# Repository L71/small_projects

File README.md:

Some minor projects

* Eurorack blank panels (Ponoko design)
* Eurorack power supply to breadboard adapter
* Eurorack tiny current measurement help PCB
* E-Switch TL2285 breadboard adapter
* Eurorack Mini PSU (switching w Tracopower switch DC converter)
* Breadboard PSU for synth experiments, provides +/- 12V from a USB PSU
* Capacitive touch pad 2x2 test board
* Eurorack +5V adapter with DC-DC converter to get +5V from the -12V rail

These projects are licensed CC BY-SA, Lars Bengtsson 2015-2016.
https://creativecommons.org/licenses/

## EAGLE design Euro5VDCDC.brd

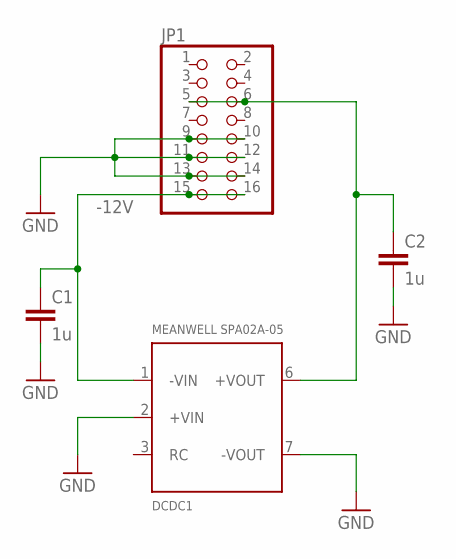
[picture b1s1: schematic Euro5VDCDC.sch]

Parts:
C1, C2: 1u; C1206K
DCDC1: MEANWELL SPA02A-05; MEANWELL_SPA02
JP1: PINHD-2X8; 2X08

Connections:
-12V: C1.1, DCDC1.1 (-VIN), JP1.15, JP1.16
GND: C1.2, C2.2, DCDC1.2 (+VIN), DCDC1.7 (-VOUT), JP1.9, JP1.10, JP1.11, JP1.12, JP1.13, JP1.14
unnamed: C2.1, DCDC1.6 (+VOUT), JP1.5, JP1.6

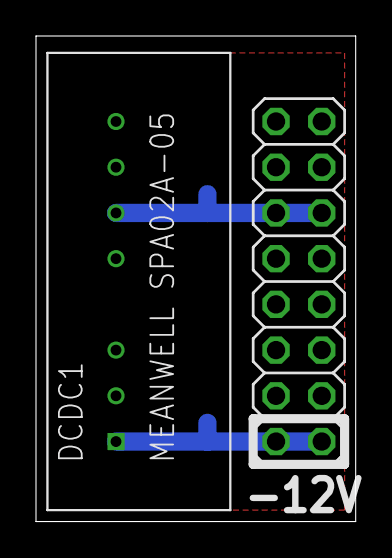
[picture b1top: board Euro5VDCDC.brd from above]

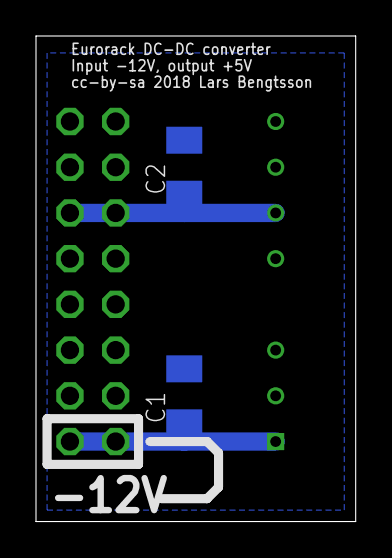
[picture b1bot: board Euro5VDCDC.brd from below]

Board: 2 copper layers, 17.8 x 27.0 mm, 4 parts (2 on the bottom side), 3 nets.

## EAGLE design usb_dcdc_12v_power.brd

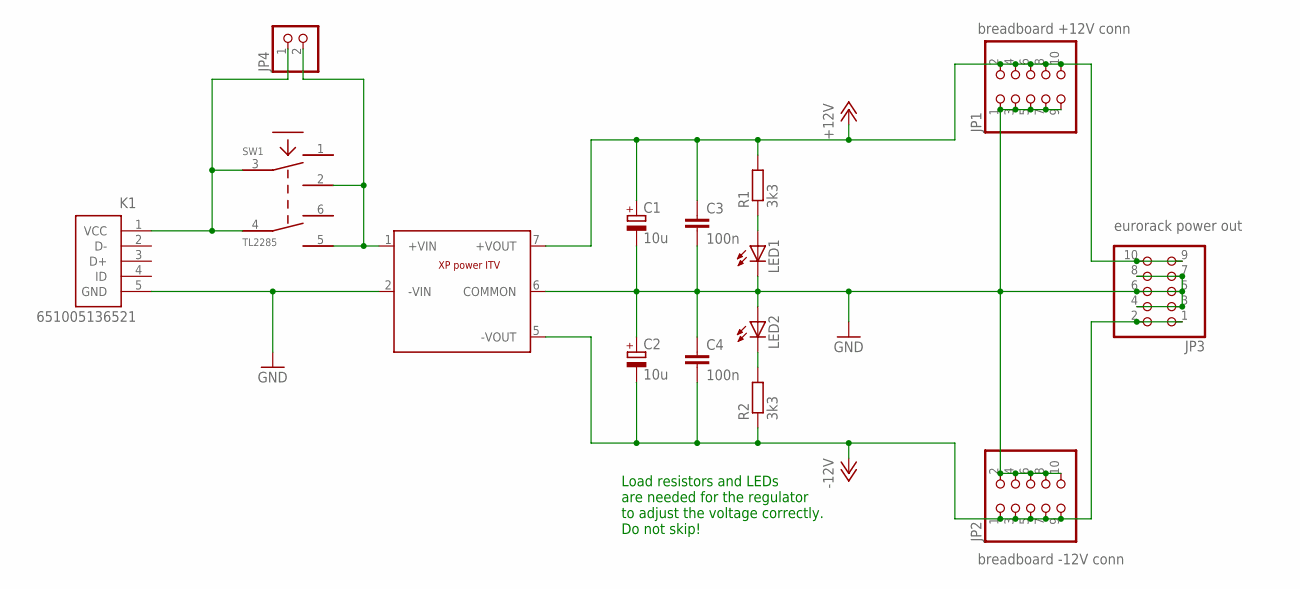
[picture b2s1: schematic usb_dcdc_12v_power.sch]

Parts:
C1, C2: 10u; E2,5-5
C3, C4: 100n; C025-025X050
JP1: breadboard +12V conn; 2X05
JP2: breadboard -12V conn; 2X05
JP3: eurorack power out; 2X05
JP4: PINHD-1X2; 1X02
K1: 651005136521
LED1, LED2: LED3MM
R1, R2: 3k3; 0207/2V
SW1: TL2285; TL2285_PCB
U$1: XP_POWER_ITV; DC_CONV_SIP_STD

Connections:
+12V: C1.+, C3.1, JP1.2, JP1.4, JP1.6, JP1.8, JP1.10, JP3.9, JP3.10, R1.2, U$1.7 (+VOUT)
-12V: C2.-, C4.2, JP2.1, JP2.3, JP2.5, JP2.7, JP2.9, JP3.1, JP3.2, R2.1, U$1.5 (-VOUT)
GND: C1.-, C2.+, C3.2, C4.1, JP1.1, JP1.3, JP1.5, JP1.7, JP1.9, JP2.2, JP2.4, JP2.6, JP2.8, JP2.10, JP3.3, JP3.4, JP3.5, JP3.6, JP3.7, JP3.8, K1.5 (GND), LED1.K (C), LED2.A, U$1.2 (-VIN), U$1.6 (COMMON)
unnamed: JP4.2, SW1.2, SW1.5, U$1.1 (+VIN)
unnamed: JP4.1, K1.1 (VCC), SW1.3, SW1.4
unnamed: LED1.A, R1.1
unnamed: LED2.K (C), R2.2

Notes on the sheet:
Load resistors and LEDs are needed for the regulator to adjust the voltage correctly. Do not skip!

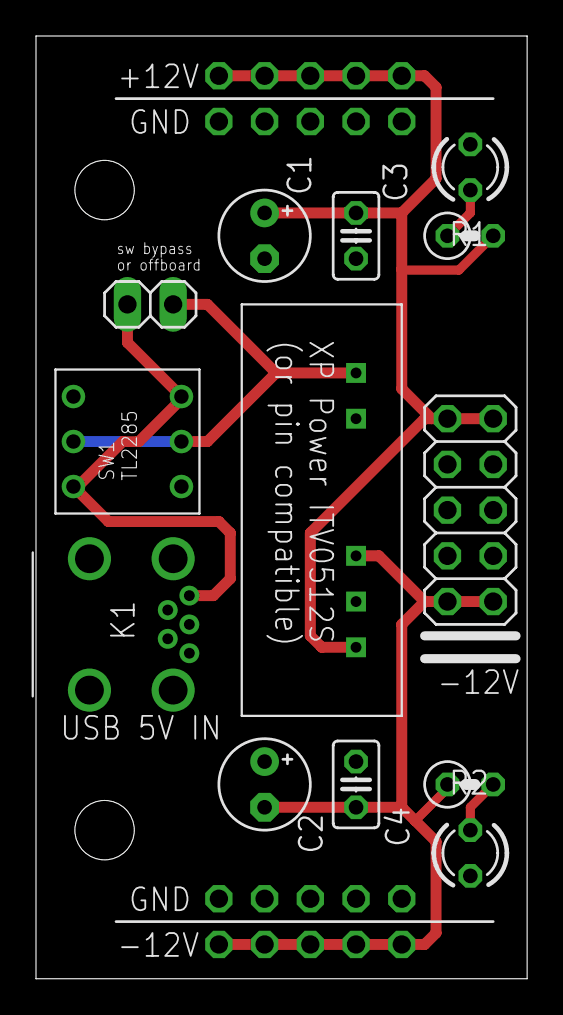
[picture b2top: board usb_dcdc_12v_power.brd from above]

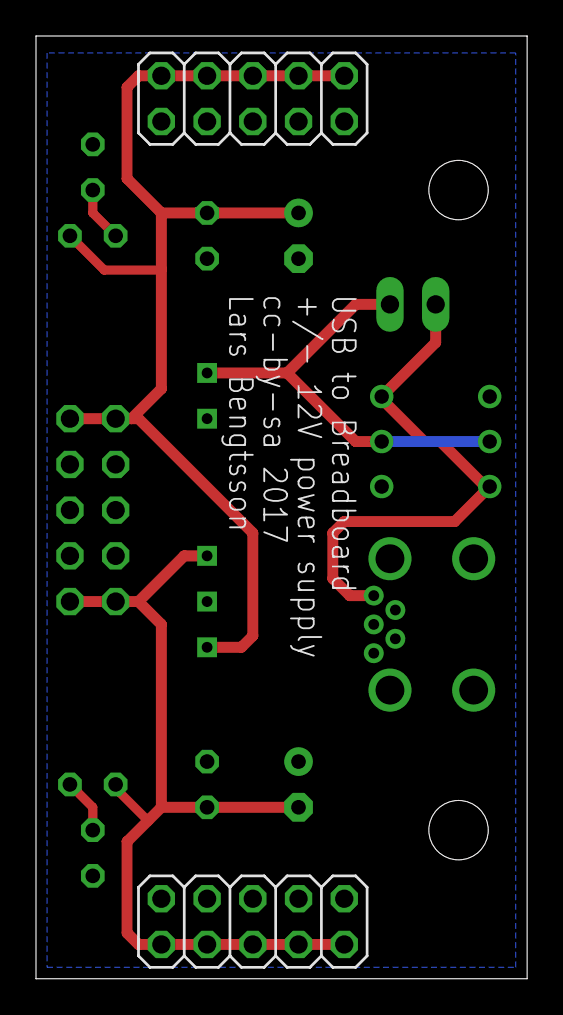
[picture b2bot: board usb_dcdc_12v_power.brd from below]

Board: 2 copper layers, 27.3 x 52.4 mm, 15 parts (2 on the bottom side), 7 nets.

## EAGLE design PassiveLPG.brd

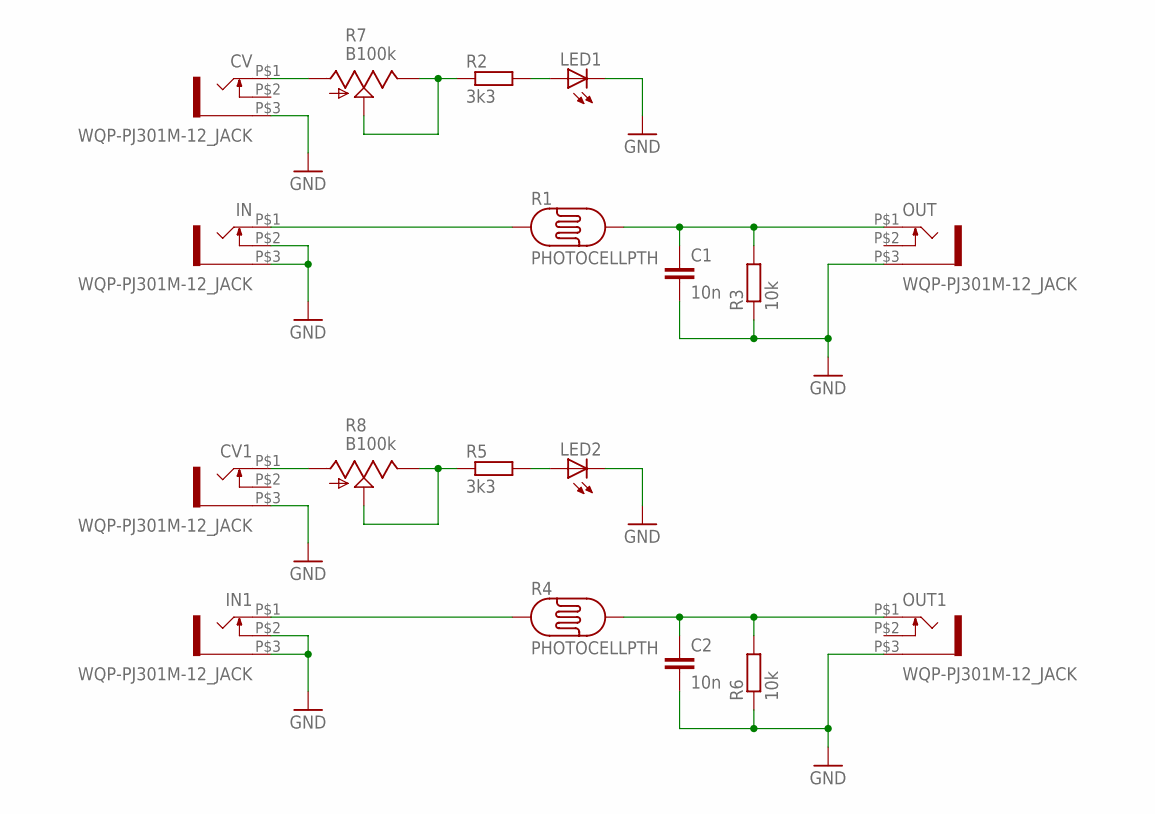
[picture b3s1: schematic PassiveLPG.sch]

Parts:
C1, C2: 10n; C050-025X075
CV, CV1: WQP-PJ301M-12_JACK
IN, IN1: WQP-PJ301M-12_JACK
LED1, LED2: LED5MM
OUT, OUT1: WQP-PJ301M-12_JACK
R1, R4: PHOTOCELLPTH; PHOTOCELL
R2, R5: 3k3; 0207/7
R3, R6: 10k; 0207/7
R7, R8: B100k; ALPS_POT_VERTICAL

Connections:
GND: C1.2, C2.2, CV.P$3 (1), CV1.P$3 (1), IN.P$2 (3), IN.P$3 (1), IN1.P$2 (3), IN1.P$3 (1), LED1.K (C), LED2.K (C), OUT.P$3 (1), OUT1.P$3 (1), R3.1, R6.1
unnamed: CV.P$1 (2), R7.P$3 (A)
unnamed: R2.1, R7.P$1 (E), R7.P$2 (S)
unnamed: IN.P$1 (2), R1.1
unnamed: C1.1, OUT.P$1 (2), R1.2, R3.2
unnamed: LED1.A, R2.2
unnamed: IN1.P$1 (2), R4.1
unnamed: C2.1, OUT1.P$1 (2), R4.2, R6.2
unnamed: R5.1, R8.P$1 (E), R8.P$2 (S)
unnamed: CV1.P$1 (2), R8.P$3 (A)
unnamed: LED2.A, R5.2

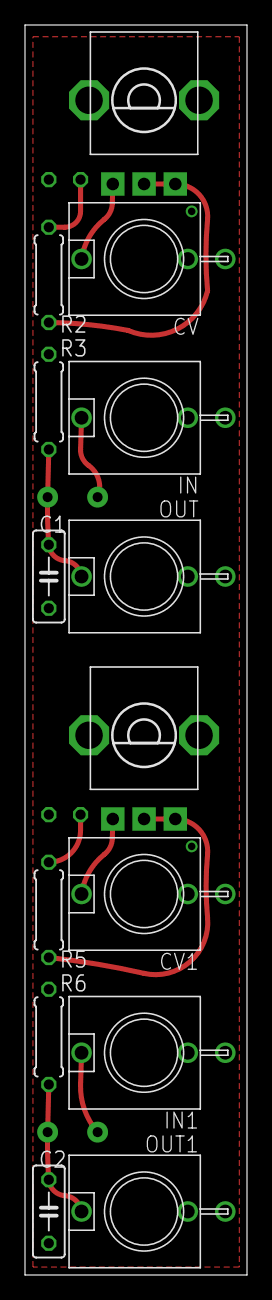
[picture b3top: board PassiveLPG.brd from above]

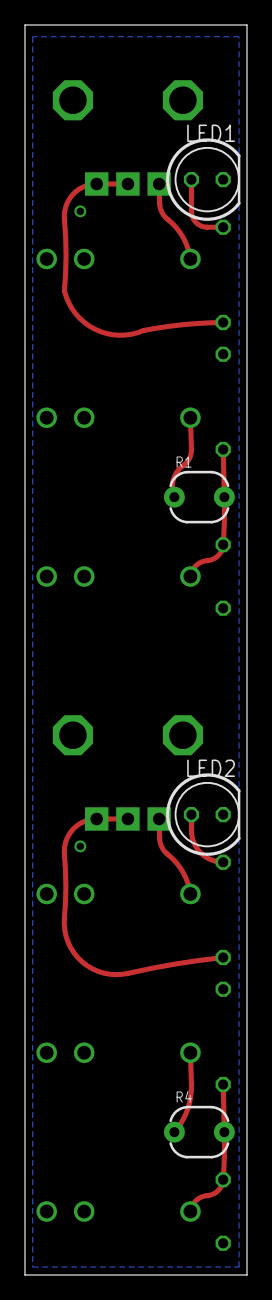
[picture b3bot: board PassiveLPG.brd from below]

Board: 2 copper layers, 17.8 x 100.0 mm, 18 parts (4 on the bottom side), 11 nets.

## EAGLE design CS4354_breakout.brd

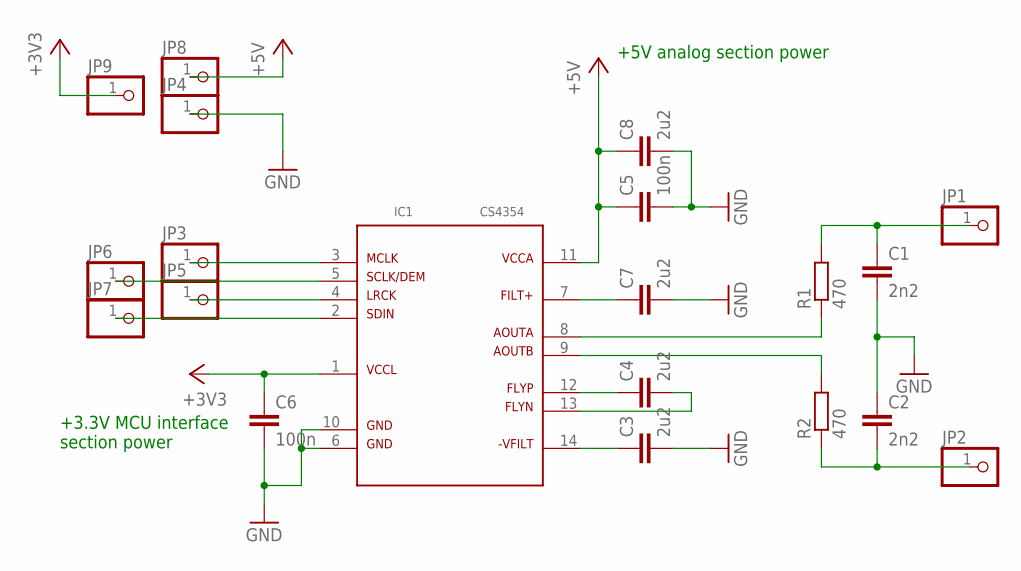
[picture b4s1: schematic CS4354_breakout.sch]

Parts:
C1, C2: 2n2; C0603K
C3, C4, C7, C8: 2u2; C0603K
C5, C6: 100n; C0603K
IC1: CS4354; SO14
JP1, JP2, JP3, JP4, JP5, JP6, JP7, JP8, JP9: PINHD-1X1; 1X01
R1, R2: 470; R0603

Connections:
+3V3: C6.1, IC1.1, JP9.1
+5V: C5.1, C8.1, IC1.11, JP8.1
AOUTA: IC1.8, R1.1
AOUTB: IC1.9, R2.2
A_OUT: C1.1, JP1.1, R1.2
B_OUT: C2.2, JP2.1, R2.1
GND: C1.2, C2.1, C3.2, C5.2, C6.2, C7.2, C8.2, IC1.6, IC1.10, JP4.1
LRCK: IC1.4, JP5.1
MCLK: IC1.3, JP3.1
unnamed: C7.1, IC1.7
unnamed: C4.1, IC1.12
unnamed: C4.2, IC1.13
unnamed: C3.1, IC1.14
SCLK: IC1.5, JP6.1
SDIN: IC1.2, JP7.1

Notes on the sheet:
+5V analog section power
+3.3V MCU interface section power

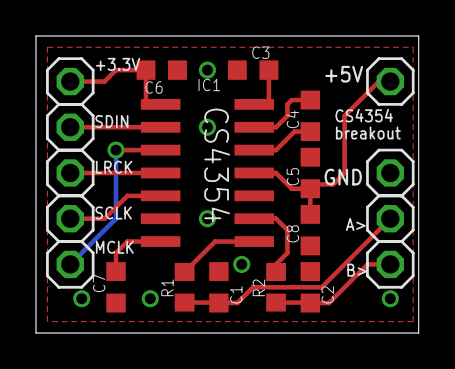
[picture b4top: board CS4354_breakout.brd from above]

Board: 2 copper layers, 21.3 x 16.5 mm, 20 parts (0 on the bottom side), 15 nets.

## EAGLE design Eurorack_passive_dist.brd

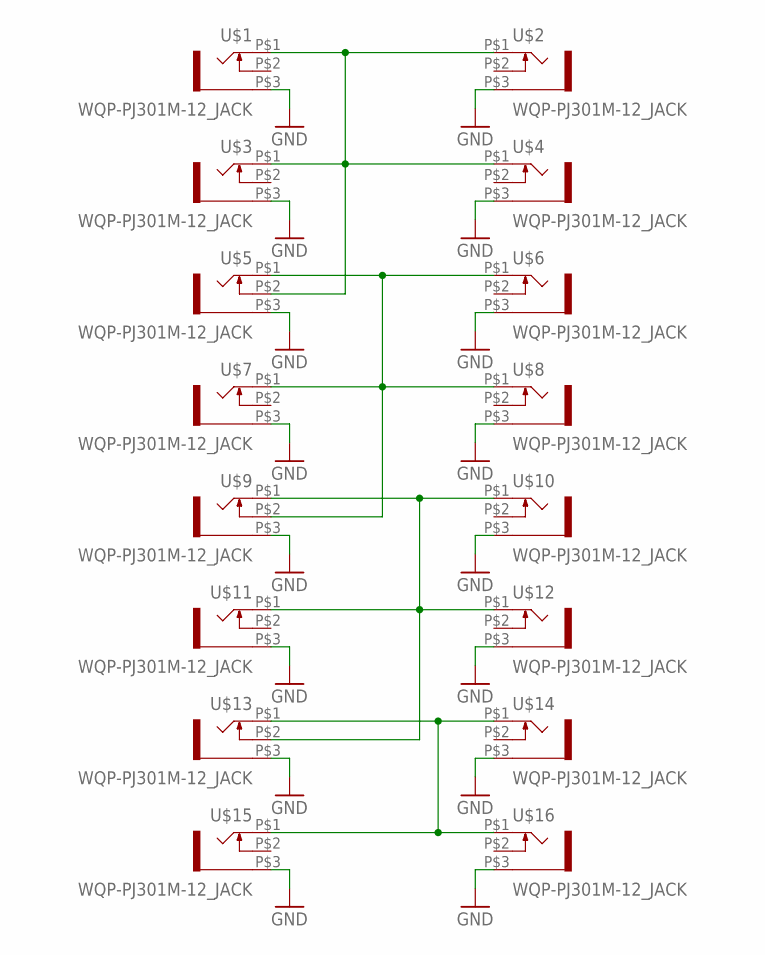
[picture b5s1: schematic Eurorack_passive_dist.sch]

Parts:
U$1, U$2, U$3, U$4, U$5, U$6, U$7, U$8, U$9, U$10, U$11, U$12, U$13, U$14, U$15, U$16: WQP-PJ301M-12_JACK

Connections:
GND: U$1.P$3 (1), U$2.P$3 (1), U$3.P$3 (1), U$4.P$3 (1), U$5.P$3 (1), U$6.P$3 (1), U$7.P$3 (1), U$8.P$3 (1), U$9.P$3 (1), U$10.P$3 (1), U$11.P$3 (1), U$12.P$3 (1), U$13.P$3 (1), U$14.P$3 (1), U$15.P$3 (1), U$16.P$3 (1)
unnamed: U$1.P$1 (2), U$2.P$1 (2), U$3.P$1 (2), U$4.P$1 (2), U$5.P$2 (3)
unnamed: U$5.P$1 (2), U$6.P$1 (2), U$7.P$1 (2), U$8.P$1 (2), U$9.P$2 (3)
unnamed: U$9.P$1 (2), U$10.P$1 (2), U$11.P$1 (2), U$12.P$1 (2), U$13.P$2 (3)
unnamed: U$13.P$1 (2), U$14.P$1 (2), U$15.P$1 (2), U$16.P$1 (2)

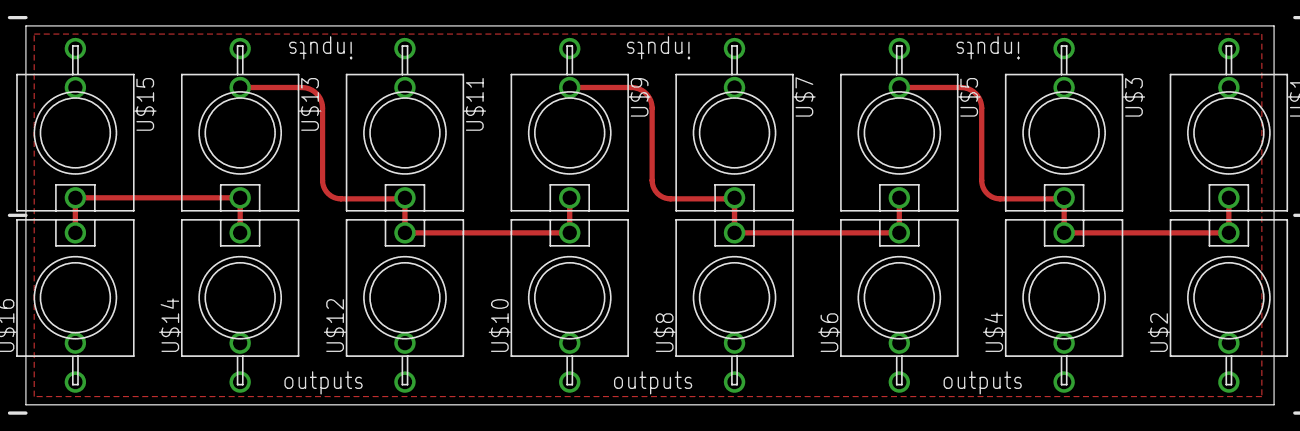
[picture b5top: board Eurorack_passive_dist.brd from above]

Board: 2 copper layers, 96.2 x 29.2 mm, 16 parts (0 on the bottom side), 5 nets.

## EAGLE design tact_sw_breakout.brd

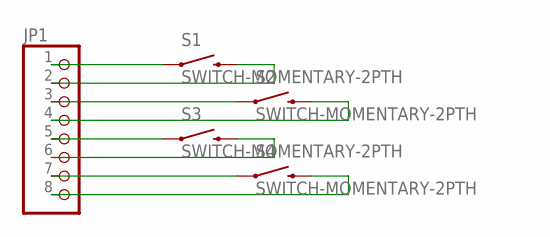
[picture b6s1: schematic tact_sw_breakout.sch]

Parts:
JP1: PINHD-1X8; 1X08
S1, S2, S3, S4: SWITCH-MOMENTARY-2PTH; TACTILE-PTH

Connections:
unnamed: JP1.1, S1.1
unnamed: JP1.2, S1.3 (2)
unnamed: JP1.3, S2.1
unnamed: JP1.5, S3.1
unnamed: JP1.7, S4.1
unnamed: JP1.4, S2.3 (2)
unnamed: JP1.6, S3.3 (2)
unnamed: JP1.8, S4.3 (2)

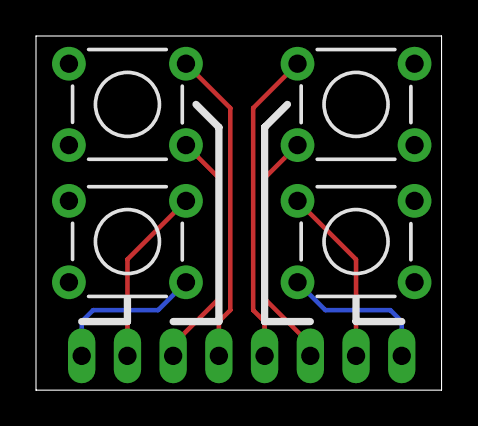
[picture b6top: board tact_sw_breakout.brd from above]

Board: 2 copper layers, 22.5 x 19.7 mm, 5 parts (1 on the bottom side), 8 nets.

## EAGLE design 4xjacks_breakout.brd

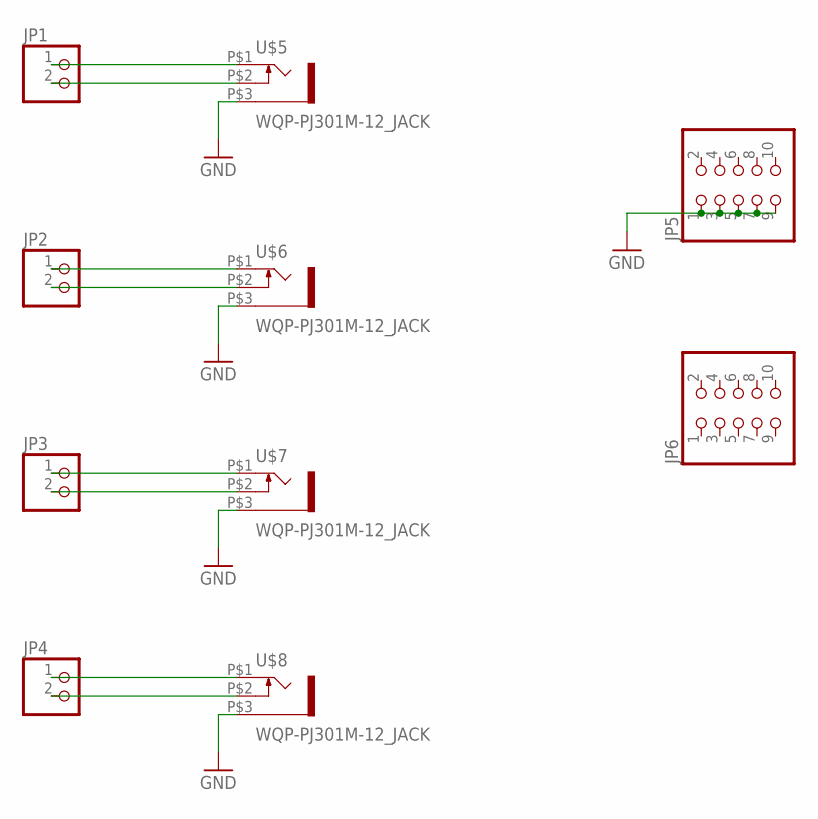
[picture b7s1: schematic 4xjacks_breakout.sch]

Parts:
JP1, JP2, JP3, JP4: PINHD-1X2; 1X02
JP5, JP6: PINHD-2X5; 2X05
U$5, U$6, U$7, U$8: WQP-PJ301M-12_JACK

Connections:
GND: JP5.1, JP5.3, JP5.5, JP5.7, JP5.9, U$5.P$3 (1), U$6.P$3 (1), U$7.P$3 (1), U$8.P$3 (1)
unnamed: JP1.1, U$5.P$1 (2)
unnamed: JP1.2, U$5.P$2 (3)
unnamed: JP2.1, U$6.P$1 (2)
unnamed: JP2.2, U$6.P$2 (3)
unnamed: JP3.1, U$7.P$1 (2)
unnamed: JP3.2, U$7.P$2 (3)
unnamed: JP4.1, U$8.P$1 (2)
unnamed: JP4.2, U$8.P$2 (3)

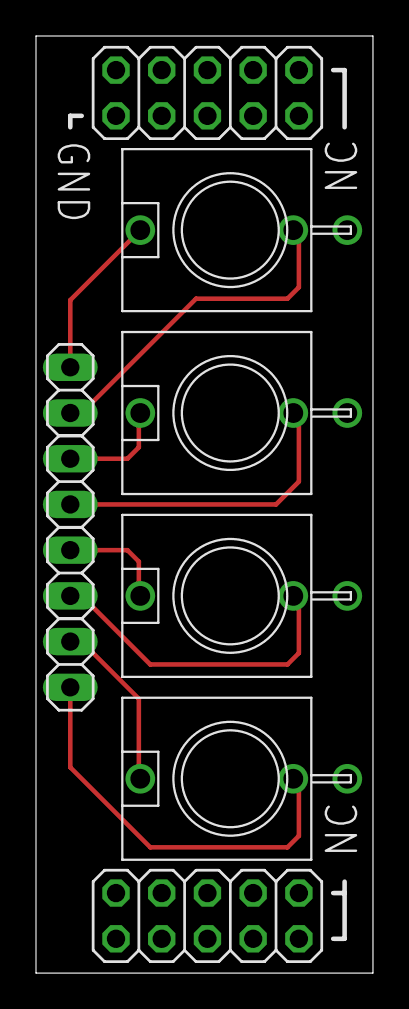
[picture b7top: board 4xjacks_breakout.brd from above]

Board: 2 copper layers, 18.7 x 52.1 mm, 10 parts (0 on the bottom side), 9 nets.

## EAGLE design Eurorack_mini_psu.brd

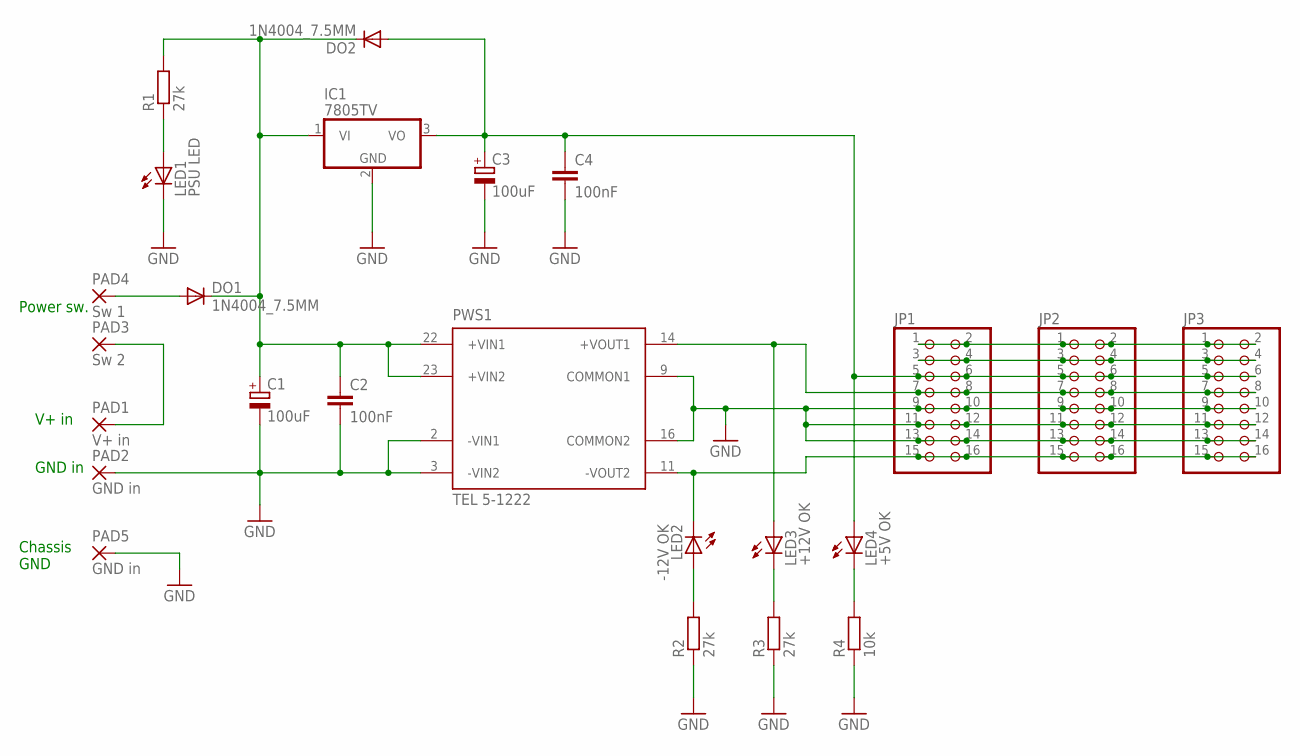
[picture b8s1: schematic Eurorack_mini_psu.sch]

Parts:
C1, C3: 100uF; E2,5-6
C2, C4: 100nF; C025-025X050
DO1, DO2: 1N4004_7.5MM; DO41-7
IC1: 7805TV; TO220V
JP1, JP2, JP3: PINHD-2X8; 2X08
LED1: PSU LED; LED3MM
LED2: -12V OK; LED3MM
LED3: +12V OK; LED3MM
LED4: +5V OK; LED3MM
PAD1: V+ in; 2,15/1,0
PAD2, PAD5: GND in; 2,15/1,0
PAD3: Sw 2; 2,15/1,0
PAD4: Sw 1; 2,15/1,0
PWS1: TEL 5-1222; TEN3XXXX
R1, R2, R3: 27k; 0207/7
R4: 10k; 0207/7

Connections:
+5V: C3.+, C4.1, DO2.A, IC1.3 (VO), JP1.5, JP1.6, JP2.5, JP2.6, JP3.5, JP3.6, LED4.A
+12V: JP1.7, JP1.8, JP2.7, JP2.8, JP3.7, JP3.8, LED3.A, PWS1.14 (+VOUT1)
-12V: JP1.15, JP1.16, JP2.15, JP2.16, JP3.15, JP3.16, LED2.K (C), PWS1.11 (-VOUT2)
GND: C1.-, C2.2, C3.-, C4.2, IC1.2 (GND), JP1.9, JP1.10, JP1.11, JP1.12, JP1.13, JP1.14, JP2.9, JP2.10, JP2.11, JP2.12, JP2.13, JP2.14, JP3.9, JP3.10, JP3.11, JP3.12, JP3.13, JP3.14, LED1.K (C), PAD2.1, PAD5.1, PWS1.2 (-VIN1), PWS1.3 (-VIN2), PWS1.9 (COMMON1), PWS1.16 (COMMON2), R2.1, R3.1, R4.1
unnamed: JP1.3, JP1.4, JP2.3, JP2.4, JP3.3, JP3.4
unnamed: PAD1.1, PAD3.1
unnamed: DO1.A, PAD4.1
unnamed: C1.+, C2.1, DO1.C, DO2.C, IC1.1 (VI), PWS1.22 (+VIN1), PWS1.23 (+VIN2), R1.2
unnamed: JP1.1, JP1.2, JP2.1, JP2.2, JP3.1, JP3.2
unnamed: LED2.A, R2.2
unnamed: LED3.K (C), R3.2
unnamed: LED4.K (C), R4.2
unnamed: LED1.A, R1.1

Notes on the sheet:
V+ in
GND in
Power sw.
Chassis GND

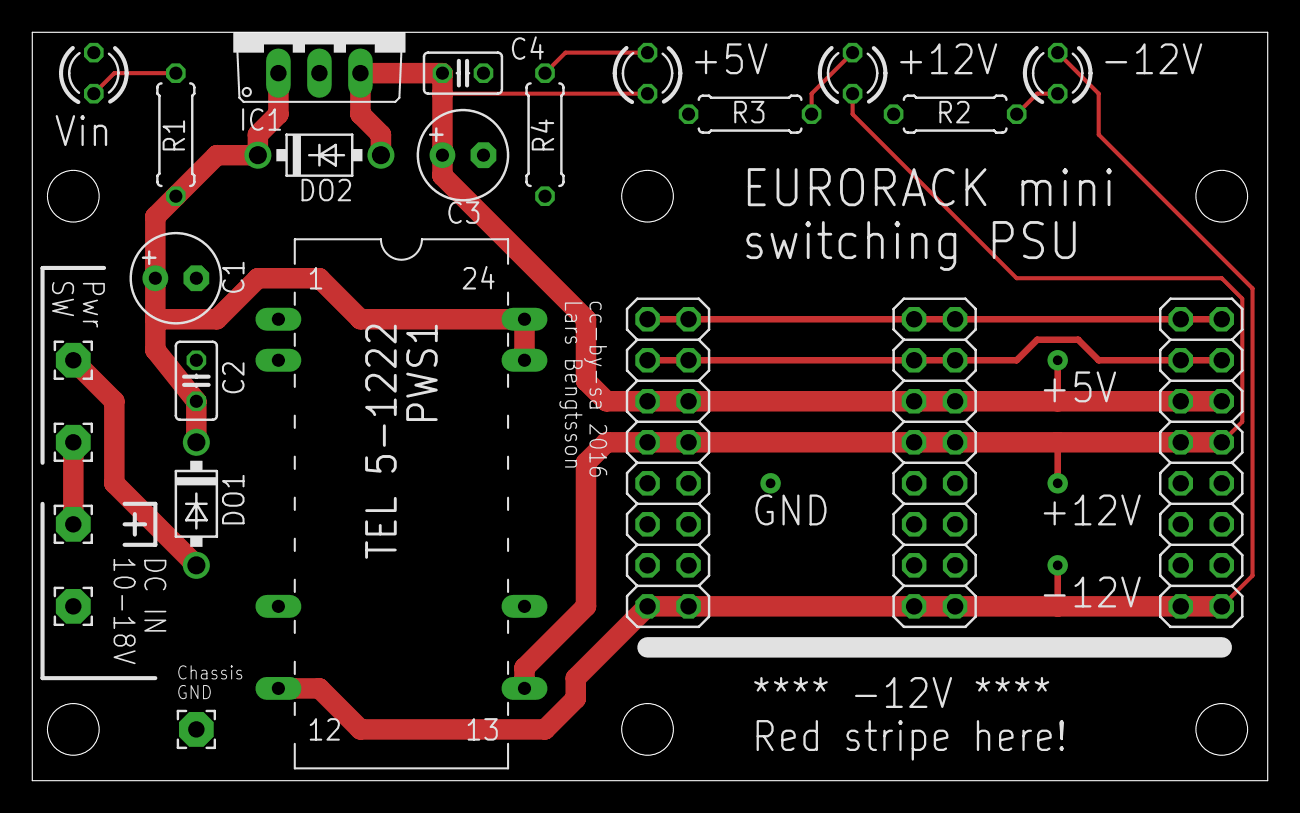
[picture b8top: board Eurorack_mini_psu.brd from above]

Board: 2 copper layers, 76.5 x 46.3 mm, 24 parts (0 on the bottom side), 13 nets.

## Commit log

2016-03-19 Initial add.
2016-03-19 Initial add to repo.
2016-03-19 Added readme.
2016-03-19 Updates PCB labels.
2016-04-06 Moved bottom holes 1/40" down, should better fit cases with 3mm screw rails.
2016-05-18 Breadboard PCB with 4x thonkiconn 3.5mm jacks.
2016-05-18 Breadboard breakout PCB with 4x tact switches
2016-05-18 Eurorack passive signal distribution module, PCB and panel drawings for Ponoko.
2016-05-18 Object-to-path on texts.
2016-05-22 Engraving fixes.
2017-02-12 Cirrus Logic CS4354 audio DAC breakout board
2017-03-11 Initial upload.
2018-06-19 Committing apparently modified files... :)
2018-06-19 4 button capacitive touch pad for breadboard experiments
2018-06-19 Breadboard power supply board with DC-DC converter, will give +/- 12V (about 40mA) from a 5V USB supply.
2018-06-19 Eurorack +5V power supply module, uses a DC-DC converter to create +5V from the -12V power supply rail.
2018-06-19 updated notes.
2018-06-19 Fixes: smaller pads, no grounding pins.

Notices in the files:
4xjacks_breakout.brd:
cc-by-sa 2016 Lars Bengtsson
CS4354_breakout.brd:
CC-BY-SA 2017
Euro5VDCDC.brd:
cc-by-sa 2018 Lars Bengtsson
Eurorack_mini_psu.brd:
cc-by-sa 2016
parts and their libraries:
SparkFun-Sensors: Licensing: Creative Commons ShareAlike 4.0 International - https://creativecommons.org/licenses/by-sa/4.0
Wuerth_Elektronik_eiCan_Communication_Co: Copyright: Würth Elektronik
